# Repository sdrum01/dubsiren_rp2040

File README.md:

# DUB-IY Dub Siren with RP2040 CPU

DUBSIREN_rp2040 is a project designed to emulate a analog frequency generator for dub and reggae music. The result is the "**DUB-IY**" dub siren. 

Dub sirens are simple synthesizers without VCA (Voltage Controlled Amplifier) or VCF (Voltage Controlled Filter), but usually with a VCO (Voltage Controlled Oscillator) modulated by an LFO (Low Frequency Generator).

Such sirens are typically built with analog circuits. The challenge, however, was to optimize the parameter storage of digital solutions, simplify the electronics and to make it hackable.

**DUB-IY** is based on a Raspberry Pi Pico with an RP2040 CPU. It is fast enough to emulate VCOs and LFOs and offers sufficient options for internal data storage.

The Dub siren creates an square wave signal with an adjustable duty cycle. The sound can be modulated by two LFOs and an envelope generator to modulate the timing parameter. 

Finally, the signal is perfected with an integrated echo effect. 

The following values can be adjusted using potentiometers and switches:

* LFO1 waveform
(square, triple square, triangle, sawtooth, pulse)
* LFO2 waveform (square, triangle, sawtooth)
* Oscillator base frequency
* LFO1 and LFO2 frequency
* LFO1 and LFO2 contribution (negative and positive)
* Timing envelope contribution
* Oscillator waveform duty cycle
* LFO start retriggering
* Delay time (echo)
* Feedback (echo)
* Overall volume

The combination of LFOs 1 and 2 already produces many experimental siren sounds,
but the timing envelope adds significantly more dynamics to the sound.

>[!NOTE]
   >
   >This is a non-profit project with no goal of making big money.
   >It's purely for fun, and we assume no liability!
   
## Waiting List

To reserve one device or PCB pls write me an email: dub-iy@sdrum.elementfx.com

## Documentation

Have a look into the short introduction on YouTube:

- [DUB-IY Introduction](https://youtu.be/Yc06HZqR8gg?si=ktLNwQYJj4XRiWYL) 

There is also a manual explaining the various functions:

- [English Manual](docs/en/index.md)
- [Kurzanleitung Deutsch](docs/de/index.md)

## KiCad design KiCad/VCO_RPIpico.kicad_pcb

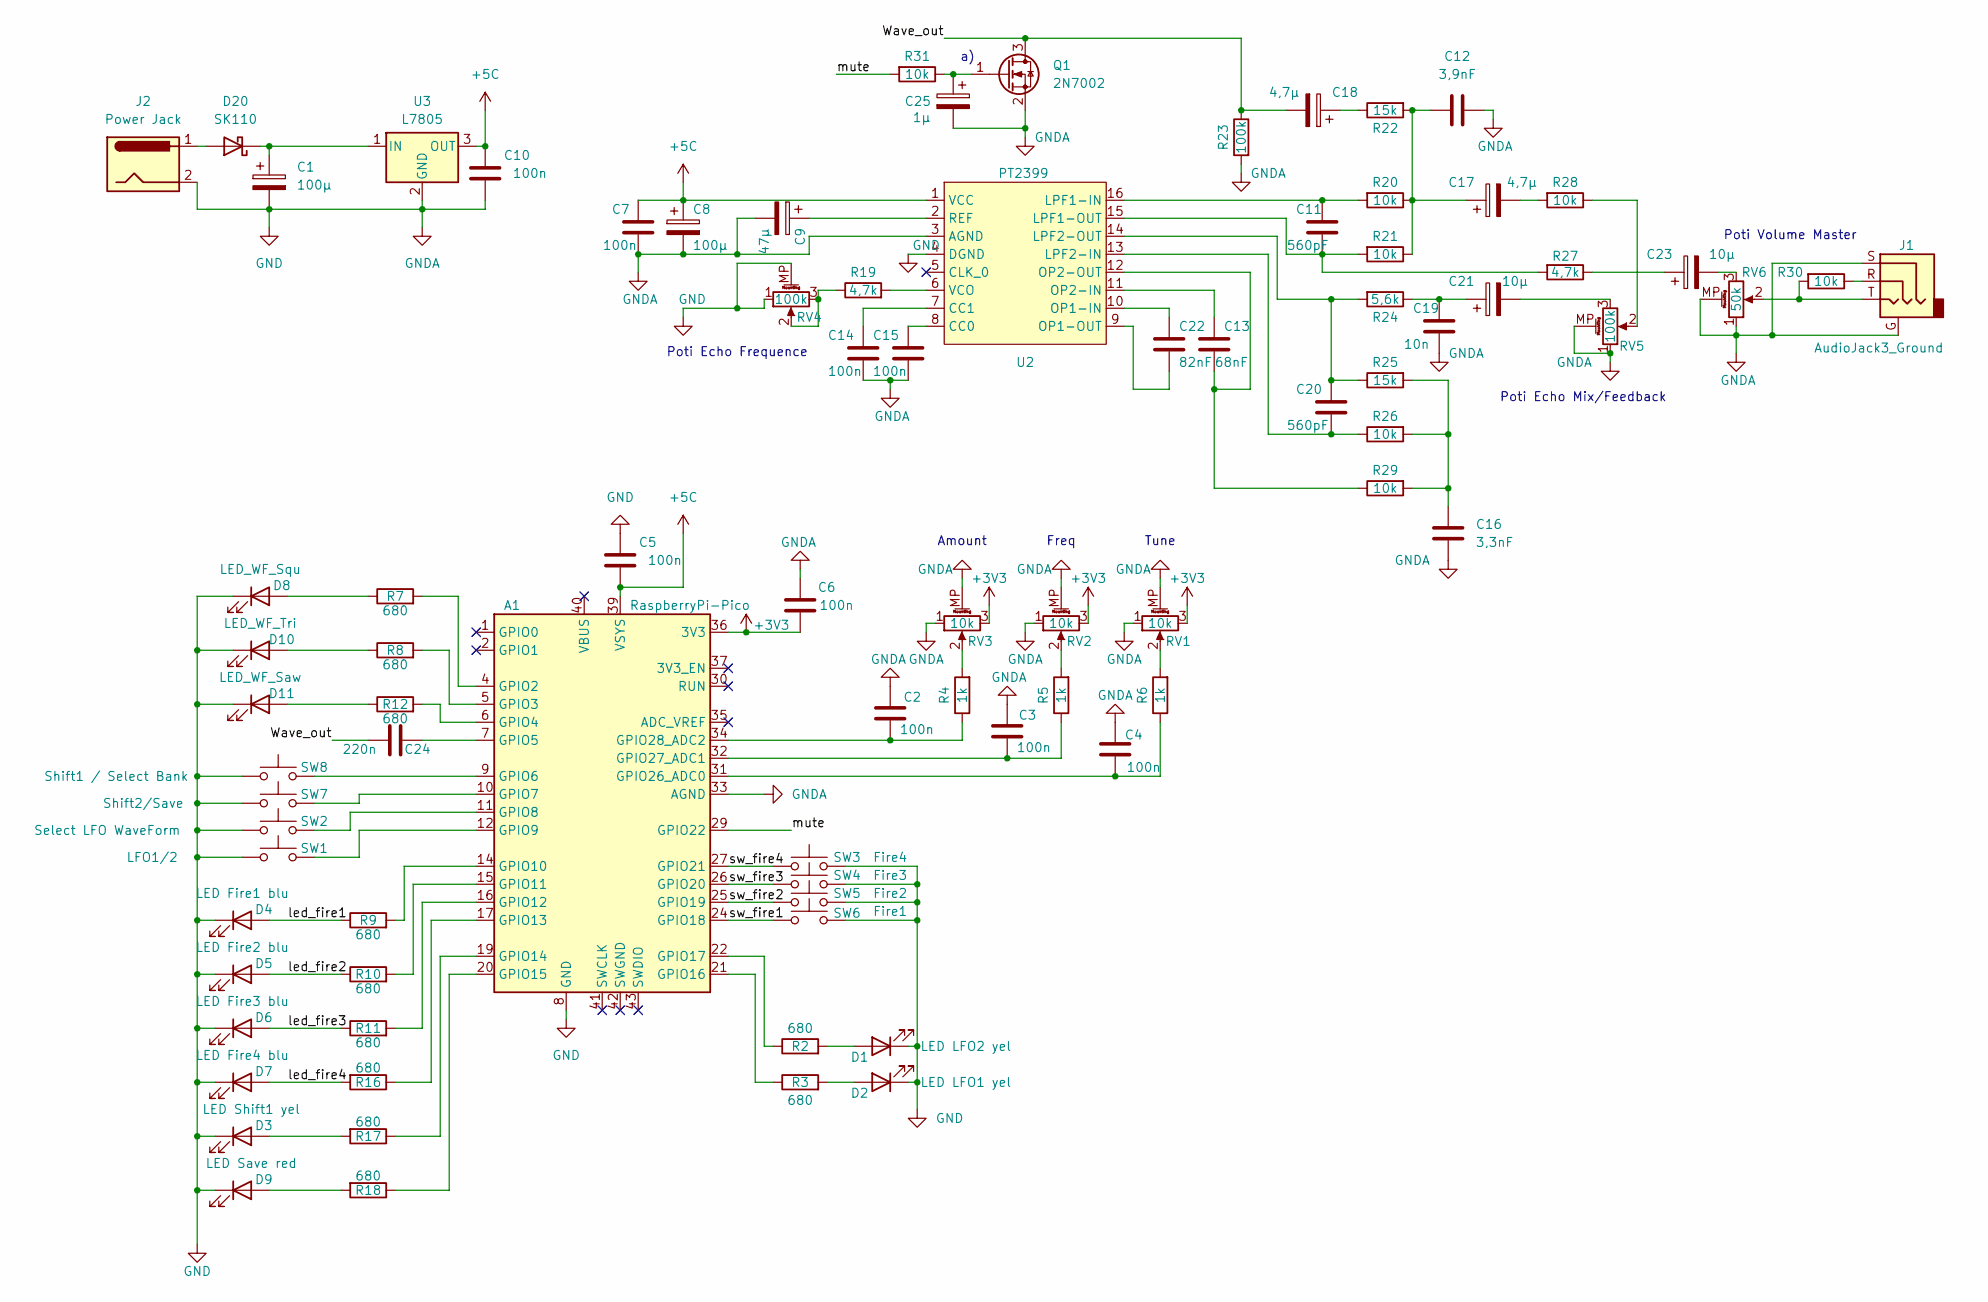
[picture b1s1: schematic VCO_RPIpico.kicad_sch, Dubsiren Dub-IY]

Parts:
A1: RaspberryPi-Pico; RPi_Pico_SMD_TH
C1, C8: 100µ; CP_Elec_6.3x5.8
C2, C3, C4, C5, C6, C7: 100n; C_1206_3216Metric
C9: 47µ; CP_Elec_6.3x5.3
C10, C14, C15: 100n; C_0805_2012Metric_Pad1.18x1.45mm_HandSolder
C11, C20: 560pF; C_0805_2012Metric_Pad1.18x1.45mm_HandSolder
C12: 3,9nF; C_0805_2012Metric_Pad1.18x1.45mm_HandSolder
C13: 68nF; C_0805_2012Metric_Pad1.18x1.45mm_HandSolder
C16: 3,3nF; C_0805_2012Metric_Pad1.18x1.45mm_HandSolder
C17, C18: 4,7µ; CP_EIA-2012-12_Kemet-R_Pad1.30x1.05mm_HandSolder
C19: 10n; C_0805_2012Metric_Pad1.18x1.45mm_HandSolder
C21, C23: 10µ; CP_Elec_4x5.7
C22: 82nF; C_0805_2012Metric_Pad1.18x1.45mm_HandSolder
C24: 220n; C_1206_3216Metric
C25: 1µ; CP_EIA-2012-12_Kemet-R_Pad1.30x1.05mm_HandSolder
D1: LED LFO2 yel; LED_D3.0mm
D2: LED LFO1 yel; LED_D3.0mm
D3: LED Shift1 yel; LED_D3.0mm
D4: LED Fire1 blu; LED_D3.0mm
D5: LED Fire2 blu; LED_D3.0mm
D6: LED Fire3 blu; LED_D3.0mm
D7: LED Fire4 blu; LED_D3.0mm
D8: LED_WF_Squ; LED_D3.0mm
D9: LED Save red; LED_D3.0mm
D10: LED_WF_Tri; LED_D3.0mm
D11: LED_WF_Saw; LED_D3.0mm
D20: SK110; D_SMA-SMB_Universal_Handsoldering
J1: AudioJack3_Ground; Jack_6.35mm_Neutrik_NMJ6HFD2_Horizontal
J2: Power Jack; BarrelJack_GCT_DCJ200-10-A_Horizontal
Q1: 2N7002; SOT-23
R2, R3, R7, R8, R9, R10, R11, R12, R16, R17, R18: 680; R_1206_3216Metric
R4, R5, R6: 1k; R_1206_3216Metric
R19, R27: 4,7k; R_1206_3216Metric
R20, R21, R26, R28, R29, R30, R31: 10k; R_1206_3216Metric
R22, R25: 15k; R_1206_3216Metric
R23: 100k; R_1206_3216Metric
R24: 5,6k; R_1206_3216Metric
RV1, RV2, RV3: 10k; Potentiometer_Alps_RK09K_Single_Vertical
RV4, RV5: 100k; Potentiometer_Alps_RK09K_Single_Vertical
RV6: 50k; Potentiometer_Alps_RK09K_Single_Vertical
SW1: LFO1/2; SW_PUSH_6mm
SW2: Select LFO WaveForm; SW_PUSH_6mm
SW3: Fire4; SW_PUSH_6mm
SW4: Fire3; SW_PUSH_6mm
SW5: Fire2; SW_PUSH_6mm
SW6: Fire1; SW_PUSH_6mm
SW7: Shift2/Save; SW_PUSH_6mm
SW8: Shift1 / Select Bank; SW_PUSH_6mm
U2: PT2399; DIP-16_W7.62mm_Socket_LongPads
U3: L7805; TO-252-3_TabPin2

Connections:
+3V3: A1.36 (3V3), C6.2, RV1.3, RV2.3, RV3.3
+5C: A1.39 (VSYS), C5.2, C7.1, C8.1, C10.1, U2.1 (VCC), U3.3 (OUT)
/Wave_out: C18.2, C24.1, Q1.3 (D), R23.1
/led_fire1: D4.2 (A), R9.1
/led_fire2: D5.2 (A), R10.1
/led_fire3: D6.2 (A), R11.1
/led_fire4: D7.2 (A), R16.2
/sw_fire1: A1.24 (GPIO18), SW6.1
/sw_fire2: A1.25 (GPIO19), SW5.1
/sw_fire3: A1.26 (GPIO20), SW4.1
/sw_fire4: A1.27 (GPIO21), SW3.1
GND: A1.3 (GND), A1.8 (GND), A1.13 (GND), A1.18 (GND), A1.23 (GND), A1.28 (GND), A1.33 (AGND), A1.38 (GND), C1.2, C2.1, C3.1, C4.1, C5.1, C6.1, C7.2, C8.2, C9.2, C10.2, C12.1, C14.2, C15.2, C16.2, C19.2, C25.2, D1.1 (K), D2.1 (K), D3.1 (K), D4.1 (K), D5.1 (K), D6.1 (K), D7.1 (K), D8.1 (K), D9.1 (K), D10.1 (K), D11.1 (K), J1.G, J1.S, J2.2, Q1.2 (S), R23.2, RV1.1, RV1.MP (MountPin), RV2.1, RV2.MP (MountPin), RV3.1, RV3.MP (MountPin), RV4.1, RV4.MP (MountPin), RV5.1, RV5.MP (MountPin), RV6.1, RV6.MP (MountPin), SW1.1, SW2.1, SW3.2, SW4.2, SW5.2, SW6.2, SW7.1, SW8.1, U2.3 (AGND), U2.4 (DGND), U3.2 (GND)
unnamed: A1.4 (GPIO2), R7.2
unnamed: A1.5 (GPIO3), R8.2
unnamed: A1.6 (GPIO4), R12.2
unnamed: A1.7 (GPIO5), C24.2
unnamed: A1.9 (GPIO6), SW8.2
unnamed: A1.10 (GPIO7), SW7.2
unnamed: A1.11 (GPIO8), SW2.2
unnamed: A1.12 (GPIO9), SW1.2
unnamed: A1.14 (GPIO10), R9.2
unnamed: A1.15 (GPIO11), R10.2
unnamed: A1.16 (GPIO12), R11.2
unnamed: A1.17 (GPIO13), R16.1
unnamed: A1.19 (GPIO14), R17.1
unnamed: A1.20 (GPIO15), R18.1
unnamed: A1.21 (GPIO16), R3.1
unnamed: A1.22 (GPIO17), R2.1
unnamed: A1.31 (GPIO26_ADC0), C4.2, R6.1
unnamed: A1.32 (GPIO27_ADC1), C3.2, R5.1
unnamed: A1.34 (GPIO28_ADC2), C2.2, R4.1
unnamed: C12.2, C17.1, R20.1, R21.1, R22.2
unnamed: C16.1, R25.2, R26.2, R29.2
unnamed: C17.2, R28.2
unnamed: C18.1, R22.1
unnamed: C19.1, C21.1, R24.1
unnamed: C21.2, RV5.3
unnamed: C23.1, R27.1
unnamed: C23.2, RV6.3
unnamed: C25.1, Q1.1 (G), R31.1
unnamed: D1.2 (A), R2.2
unnamed: D2.2 (A), R3.2
unnamed: D3.2 (A), R17.2
unnamed: D8.2 (A), R7.1
unnamed: D9.2 (A), R18.2
unnamed: D10.2 (A), R8.1
unnamed: D11.2 (A), R12.1
unnamed: D20.2 (A), J2.1
unnamed: C1.1, D20.1 (K), U3.1 (IN)
unnamed: J1.R, R30.1
unnamed: J1.T, R30.2, RV6.2
unnamed: R4.2, RV3.2
unnamed: R5.2, RV2.2
unnamed: R6.2, RV1.2
unnamed: R19.1, RV4.2, RV4.3
unnamed: R28.1, RV5.2
unnamed: A1.29 (GPIO22), R31.2
unnamed: C15.1, U2.8 (CC0)
unnamed: C14.1, U2.7 (CC1)
unnamed: C11.1, R20.2, U2.16 (LPF1-IN)
unnamed: C11.2, R21.2, R27.2, U2.15 (LPF1-OUT)
unnamed: C20.2, R26.1, U2.13 (LPF2-IN)
unnamed: C20.1, R24.2, R25.1, U2.14 (LPF2-OUT)
unnamed: C22.1, U2.10 (OP1-IN)
unnamed: C22.2, U2.9 (OP1-OUT)
unnamed: C13.1, U2.11 (OP2-IN)
unnamed: C13.2, R29.1, U2.12 (OP2-OUT)
unnamed: C9.1, U2.2 (REF)
unnamed: R19.2, U2.6 (VCO)

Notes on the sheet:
Poti Echo Mix/Feedback
Freq
Poti Echo Frequence
Tune
Poti Volume Master
Amount

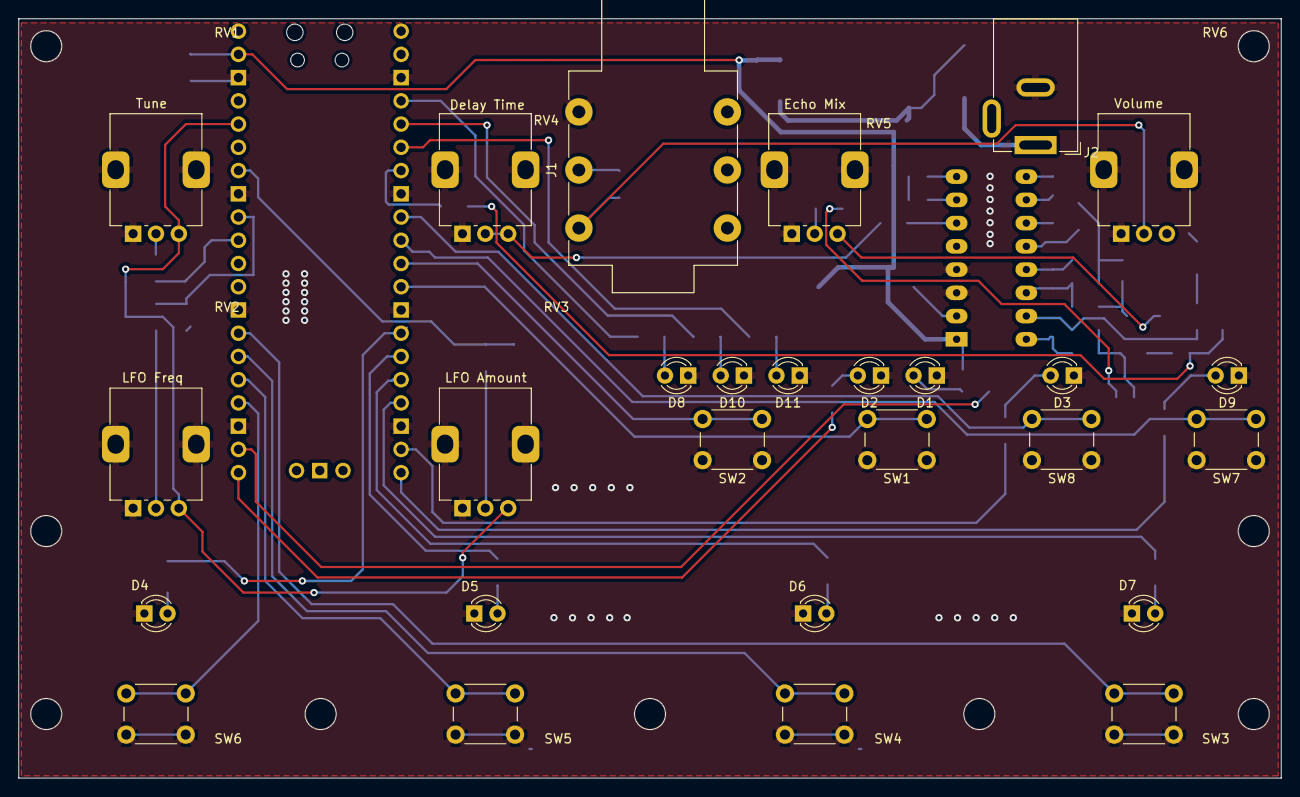
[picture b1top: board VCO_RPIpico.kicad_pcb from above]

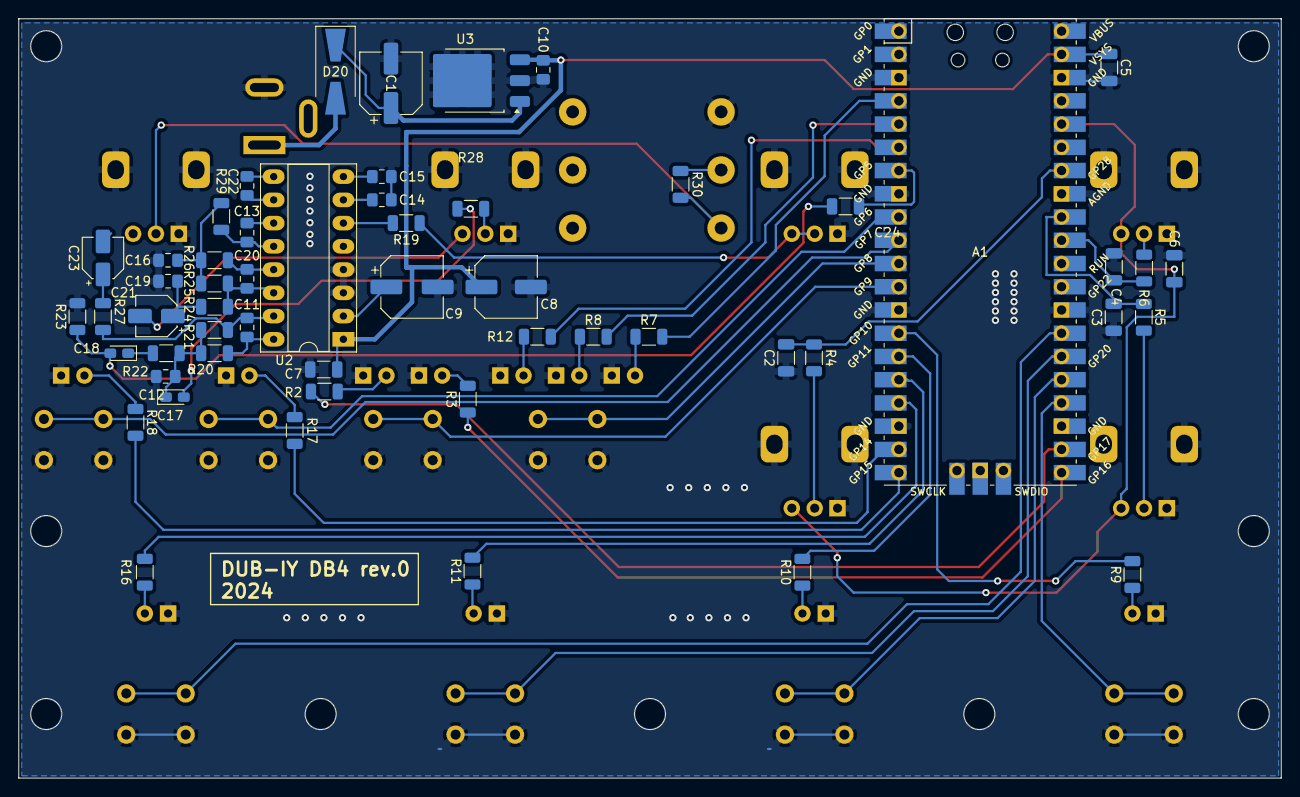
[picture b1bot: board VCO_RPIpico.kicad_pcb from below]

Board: 2 copper layers, 138.0 x 83.0 mm, 81 parts (54 on the bottom side), 67 nets.

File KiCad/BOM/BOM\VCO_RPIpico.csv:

"Reference","Value","Datasheet","Footprint","Qty","DNP","Reichelt"
"A1","RaspberryPi-Pico","https://datasheets.raspberrypi.com/pico/pico-datasheet.pdf","MCU_RaspberryPi_and_Boards:RPi_Pico_SMD_TH","1","","RASP PI PICO H "
"C1,C8","100µ","~","Capacitor_SMD:CP_Elec_6.3x5.8","2","","FT-V 100U 16 "
"C2,C3,C4,C5,C6,C7,C10,C14,C15","100n","~","-- verschiedene Werte --","9","",""
"C9","47µ","~","Capacitor_SMD:CP_Elec_6.3x5.3","1","","ELN RVS-16V470MU "
"C11,C20","560pF","~","Capacitor_SMD:C_0805_2012Metric_Pad1.18x1.45mm_HandSolder","2","",""
"C12","3,9nF","~","Capacitor_SMD:C_0805_2012Metric_Pad1.18x1.45mm_HandSolder","1","",""
"C13","68nF","~","Capacitor_SMD:C_0805_2012Metric_Pad1.18x1.45mm_HandSolder","1","",""
"C16","3,3nF","~","Capacitor_SMD:C_0805_2012Metric_Pad1.18x1.45mm_HandSolder","1","",""
"C17,C18","4,7µ","~","Capacitor_Tantalum_SMD:CP_EIA-2012-12_Kemet-R_Pad1.30x1.05mm_HandSolder","2","","KEM X5R0805 4,7U "
"C19","10n","~","Capacitor_SMD:C_0805_2012Metric_Pad1.18x1.45mm_HandSolder","1","",""
"C21,C23","10µ","~","Capacitor_SMD:CP_Elec_4x5.7","2","","SMD ELKO 10/16 "
"C22","82nF","~","Capacitor_SMD:C_0805_2012Metric_Pad1.18x1.45mm_HandSolder","1","",""
"C24","220n","~","Capacitor_SMD:C_1206_3216Metric","1","",""
"D1","LED LFO2","~","LED_THT:LED_D3.0mm","1","",""
"D2","LED LFO1","~","LED_THT:LED_D3.0mm","1","",""
"D3","LED Shift1","~","LED_THT:LED_D3.0mm","1","",""
"D4","LED Fire1","~","LED_THT:LED_D3.0mm","1","",""
"D5","LED Fire2","~","LED_THT:LED_D3.0mm","1","",""
"D6","LED Fire3","~","LED_THT:LED_D3.0mm","1","",""
"D7","LED Fire4","~","LED_THT:LED_D3.0mm","1","",""
"D8","LED_WF_Squ","~","LED_THT:LED_D3.0mm","1","",""
"D9","LED Shift2","~","LED_THT:LED_D3.0mm","1","",""
"D10","LED_WF_Tri","~","LED_THT:LED_D3.0mm","1","",""
"D11","LED_WF_Saw","~","LED_THT:LED_D3.0mm","1","",""
"D20","SK110","~","Diode_SMD:D_SMA-SMB_Universal_Handsoldering","1","",""
"J1","AudioJack3_Ground","~","Audiosockets:Jack_3.5mm_Ledino_KB3SPRS_Horizontal","1","","EBS 35 "
"J2","Power Jack","~","Connector_BarrelJack:BarrelJack_GCT_DCJ200-10-A_Horizontal","1","","CLIFF FCR681465 "
"R2,R3,R7,R8,R9,R10,R11,R12,R16,R17,R18","680","~","Resistor_SMD:R_1206_3216Metric","11","",""
"R4,R5,R6","1k","~","Resistor_SMD:R_1206_3216Metric","3","",""
"R19,R27","4,7k","~","Resistor_SMD:R_1206_3216Metric","2","",""
"R20,R21,R26,R28,R29,R30,RV1,RV2,RV3","10k","~","-- verschiedene Werte --","9","","RK09K113-LIN10K "
"R22,R25","15k","~","Resistor_SMD:R_1206_3216Metric","2","",""
"R23,RV4,RV5","100k","~","-- verschiedene Werte --","3","","RK09K113-LIN100K "
"R24","5,6k","~","Resistor_SMD:R_1206_3216Metric","1","",""
"RV6","50k","~","poti_alps:Potentiometer_Alps_RK09K_Single_Vertical","1","","RK09K113-LIN50K "
"SW1","LFO1/2","~","Button_Switch_THT:SW_PUSH_6mm","1","","OMR B3F-1002"
"SW2","Select LFO WaveForm","~","Button_Switch_THT:SW_PUSH_6mm","1","","OMR B3F-1002"
"SW3","Fire4","~","Button_Switch_THT:SW_PUSH_6mm","1","","RAFI 100.502 "
"SW4","Fire3","~","Button_Switch_THT:SW_PUSH_6mm","1","","RAFI 100.502 "
"SW5","Fire2","~","Button_Switch_THT:SW_PUSH_6mm","1","","RAFI 100.502 "
"SW6","Fire1","~","Button_Switch_THT:SW_PUSH_6mm","1","","RAFI 100.502 "
"SW7","Shift2/Save","~","Button_Switch_THT:SW_PUSH_6mm","1","","OMR B3F-1002"
"SW8","Shift1 / Select Bank","~","Button_Switch_THT:SW_PUSH_6mm","1","","OMR B3F-1002"
"U2","PT2399","","Package_DIP:DIP-16_W7.62mm_Socket_LongPads","1","",""
"U3","L7805","http://www.st.com/content/ccc/resource/technical/document/da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","Package_TO_SOT_SMD:TO-252-3_TabPin2","1","","L78M05CDT STM "

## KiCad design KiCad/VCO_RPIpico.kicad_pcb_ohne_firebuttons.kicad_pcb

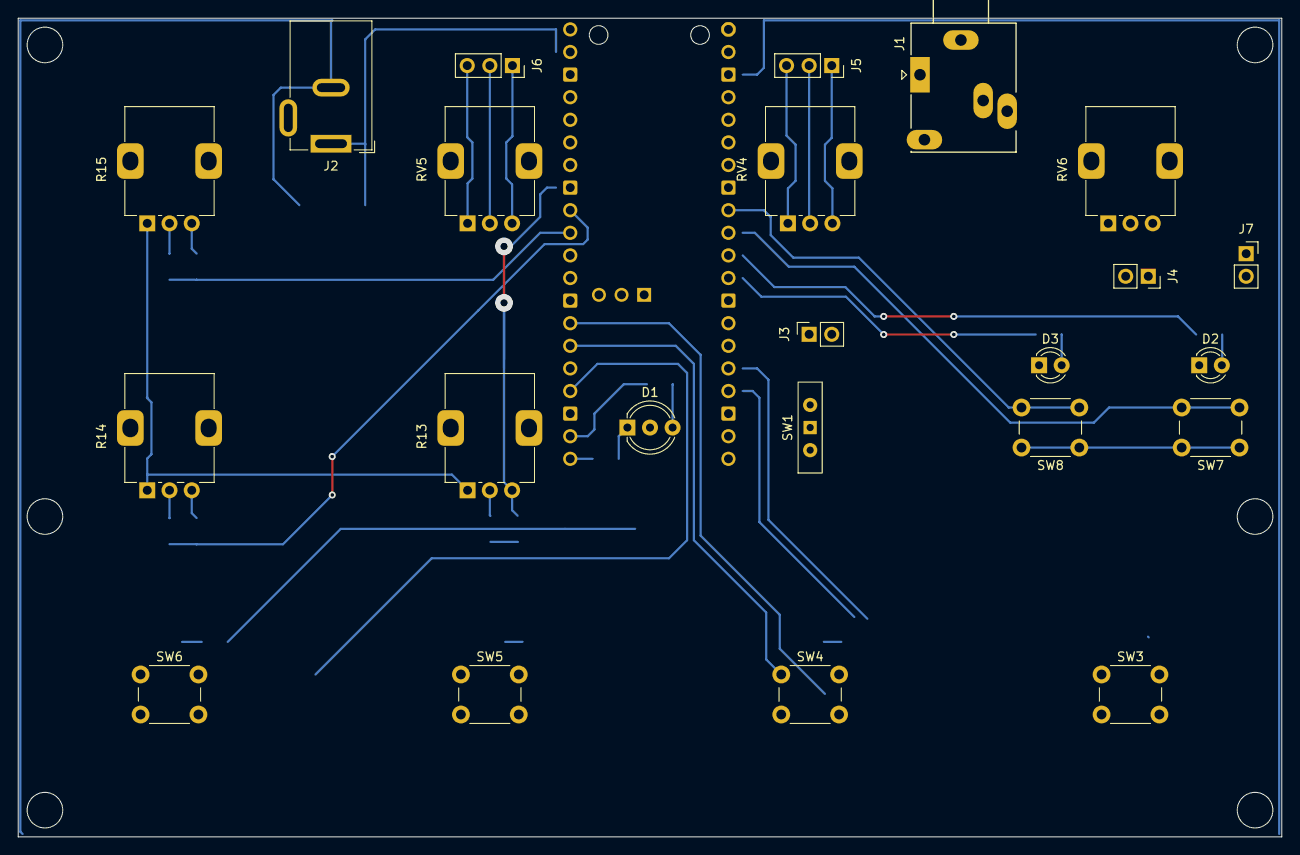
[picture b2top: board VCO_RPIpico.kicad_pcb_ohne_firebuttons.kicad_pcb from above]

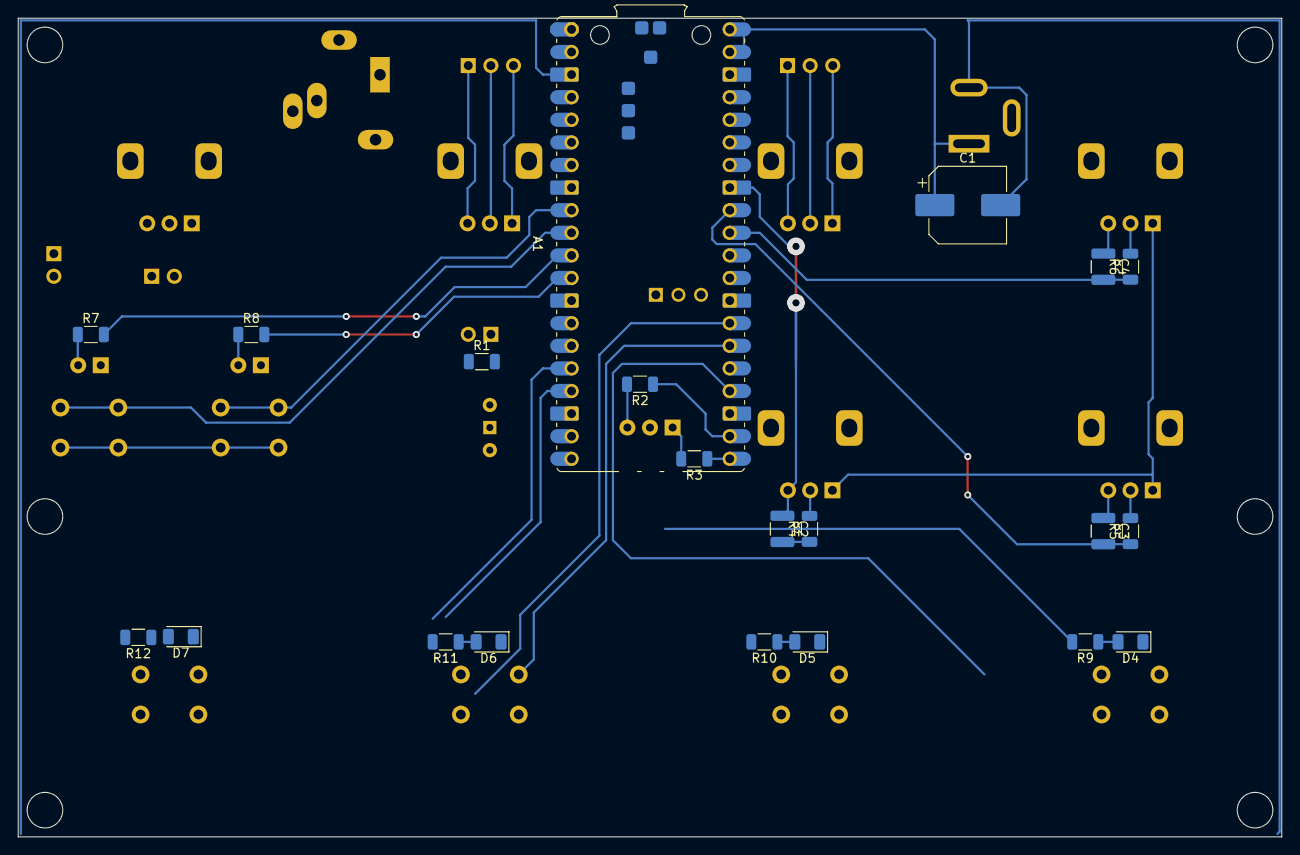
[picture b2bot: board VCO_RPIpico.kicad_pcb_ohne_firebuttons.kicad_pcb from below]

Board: 2 copper layers, 142.0 x 92.0 mm, 44 parts (21 on the bottom side), 44 nets.

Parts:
A1: RaspberryPi-Pico; Raspberry_Pi_Pico_SMT_THT_noDebugPort
C1: 100µ; CP_Elec_8x10.5
C2, C3, C4: 100n; C_1210_3225Metric
D1: LED_Dual_AKA; LED_D5.0mm-3
D2: LED Shift1; LED_D3.0mm
D3: LED Shift2; LED_D3.0mm
D4: LED Fire1; LED_1206_3216Metric
D5: LED Fire2; LED_1206_3216Metric
D6: LED Fire3; LED_1206_3216Metric
D7: LED Fire4; LED_1206_3216Metric
J1: AudioJack2; Jack_3.5mm_Ledino_KB3SPRS_Horizontal
J2: Power Jack 5V; BarrelJack_GCT_DCJ200-10-A_Horizontal
J3: Wave Out; PinSocket_1x02_P2.54mm_Vertical
J4: Echo Out; PinSocket_1x02_P2.54mm_Vertical
J5: Poti Echo Mix/Feedback; PinSocket_1x03_P2.54mm_Vertical
J6: Poti Echo Freq; PinSocket_1x03_P2.54mm_Vertical
J7: Echo Power; PinSocket_1x02_P2.54mm_Vertical
R1, R4, R5, R6: 1k; R_1206_3216Metric
R2, R3, R7, R8, R9, R10, R11, R12: 100; R_1206_3216Metric
R13, R14, R15: 100k; Potentiometer_Alps_RK09K_Single_Vertical
RV4, RV5: 100k; Potentiometer_Alps_RK09K_Single_Vertical
RV6: 50k; Potentiometer_Alps_RK09K_Single_Vertical
SW1: LFO Waveform; SW_Slide-03_Wuerth-WS-SLTV_10x2.5x6.4_P2.54mm
SW3: Fire4; SW_PUSH_6mm
SW4: Fire3; SW_PUSH_6mm
SW5: Fire2; SW_PUSH_6mm
SW6: Fire1; SW_PUSH_6mm
SW7: Shift2/Save; SW_PUSH_6mm
SW8: Shift1; SW_PUSH_6mm

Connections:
+3V3: A1.36 (3V3), R13.1, R14.1, R15.1
+5C: A1.39 (VSYS), A1.40 (VBUS), C1.1, J2.1, J7.2
GND: A1.3 (GND), A1.8 (GND), A1.13 (GND), A1.18 (GND), A1.23 (GND), A1.28 (GND), A1.38 (GND), C1.2, D1.2 (K), D2.1 (K), D3.1 (K), D4.1 (K), D5.1 (K), D6.1 (K), D7.1 (K), J1.T, J2.2, J3.1, J4.2, J7.1, RV6.1, SW1.2 (B), SW3.2, SW4.2, SW5.2, SW6.2, SW7.1, SW8.1
GNDA: A1.33 (AGND), C2.1, C3.1, C4.1, R13.3, R14.3, R15.3
unnamed: A1.5 (GPIO3), SW1.1 (A)
unnamed: A1.6 (GPIO4), SW1.3 (C)
unnamed: A1.7 (GPIO5), R1.2
unnamed: A1.9 (GPIO6), SW8.2
unnamed: A1.10 (GPIO7), SW7.2
unnamed: A1.11 (GPIO8), R7.2
unnamed: A1.12 (GPIO9), R8.2
unnamed: A1.14 (GPIO10), R9.2
unnamed: A1.15 (GPIO11), R10.2
unnamed: A1.16 (GPIO12), R11.2
unnamed: A1.17 (GPIO13), R12.2
unnamed: A1.21 (GPIO16), R3.1
unnamed: A1.22 (GPIO17), R2.1
unnamed: A1.24 (GPIO18), SW6.1
unnamed: A1.25 (GPIO19), SW5.1
unnamed: A1.26 (GPIO20), SW4.1
unnamed: A1.27 (GPIO21), SW3.1
unnamed: A1.31 (GPIO26_ADC0), C4.2, R6.1
unnamed: A1.32 (GPIO27_ADC1), C3.2, R5.1
unnamed: A1.34 (GPIO28_ADC2), C2.2, R4.1
unnamed: D1.1 (A1), R3.2
unnamed: D1.3 (A2), R2.2
unnamed: D2.2 (A), R7.1
unnamed: D3.2 (A), R8.1
unnamed: D4.2 (A), R9.1
unnamed: D5.2 (A), R10.1
unnamed: D6.2 (A), R11.1
unnamed: D7.2 (A), R12.1
unnamed: J1.S, RV6.2
unnamed: J3.2, R1.1
unnamed: J4.1, RV6.3
unnamed: J5.1, RV4.3
unnamed: J5.2, RV4.2
unnamed: J5.3, RV4.1
unnamed: J6.1, RV5.3
unnamed: J6.2, RV5.2
unnamed: J6.3, RV5.1
unnamed: R4.2, R13.2
unnamed: R5.2, R14.2
unnamed: R6.2, R15.2

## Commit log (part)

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2024-08-07 Potis abgefragt
2024-08-10 transfer LFO mit 3 Waveforms
2024-08-13 LFO Anpassungen
2024-08-15 Antilog-Konverter
2024-08-18 WaveFormFunktionsschalter für LFO und verschieben des LFO Arbeitspunkt
2024-08-27 PWM LED als Anzeige
2024-08-29 LEDs eingebunden
2024-09-02 Envelope added
2024-09-03 Envelope auf Multiplikator 1 auslaufen lassen
2024-09-04 test
2024-09-04 test dev
2024-09-04 KiCad DAten erfasst
2024-09-04 KiCad cleaned
2024-09-04 test commit
2024-09-08 Amount in die Mitte gerückt, um pos und neg Beeinflussung ohne extra Funktion zu haben
2024-09-12 Teiler für PWM bei LEDs
2024-09-15 Potiänderung auswerten
2024-09-15 littleFS test
2024-09-16 Bounce2 implementiert
2024-09-18 auf Bounce2 für Buttons umgestellt und Implementierung JSON
2024-09-19 Kicas
2024-09-19 .gitignore
2024-09-22 Speichern dere Werte per JSOM
2024-09-22 State changed on Waveformswitch
2024-09-22 Save Values and Load Values
2024-09-22 Shiftstate statt WaveformFunctions-schalter für Umschaltung der LFO/Envelop
2024-09-22 test duty
2024-09-23 gitignore angepasst
2024-09-23 Korrektur und KiCad
2024-09-26 DutyCycle added
2024-09-27 Schaltung erweitert um 2 Shhifttasten
2024-09-27 Schaltung geändert
2024-09-27 CAD-Daten aus Onshape
2024-09-28 2 Shifttasten eingebaut
2024-09-28 Shiftstate als Byte, Reset des env.durch Sh1+2
2024-09-29 logpress prepared
2024-09-29 Sound Hold with long press fire
2024-09-29 Auslenkung LFO erhöht
2024-09-30 Kicad Schematic and Board
2024-09-30 PCB and Schematic
2024-09-30 Projectfile Updated
2024-10-01 2 Shift LEDs
2024-10-02 Shift Knob Added
2024-10-02 Files added
2024-10-02 KiCad
2024-10-03 LongPress durch Drücken des Nachbarbutton und Save korrigiert
2024-10-05 LFO2 statt Envelopegenerator
2024-10-10 LFO 2 mit 3 WaveForms
2024-10-10 Envelope Test
2024-10-11 Envelope als Timing-Parameter für LFO1
2024-10-11 Envelope fertig implementiert mit Speichermöglichkeit, Bank 1..4 für Speicherplatz 1..16
2024-10-13 Testroutine Default Sound, nach Bankwechsel keine Tonerzeugung, Wechsel der Bank zum kopieren möglich
2024-10-13 Envelope auch auf LFO2
2024-10-13 debug timing wegen hänger LFO2
2024-10-13 Retriggern LFO unterdrücken bei Longpress
2024-10-14 Kicad weiter, Blink
2024-10-14 modifiziertes Boardlayout
2024-10-15 ignore mod
2024-10-15 COde workspace removed
2024-10-15 Implement Blink, Test Reset LFO2
2024-10-16 Waveform select switch
2024-10-19 KiCad weiter
2024-10-19 vom Kippschalter umgestellt auf Button zur FLO Waveform Auswahl
2024-10-20 4 LEDS für FIreButtons
2024-10-20 KiCad und Gitignore: Backups ignorieren
2024-10-22 Back to the Kippschalter als LFOWaveForm
2024-10-23 Datenblatt Schalter
2024-10-24 Korrektur StateChange und Anzeige dews letzten Firebuttons
2024-10-25 gitignore Backups CAD excluded
2024-10-27 Test Matrix
2024-10-28 KiCad MatrixLED und Bauteil für Echo
2024-10-28 remove backupd folder
2024-10-28 CAM Settings added
2024-10-28 Export STL Body
2024-10-28 noch ein Export aus CAD
2024-10-30 LED Matrix weiter
2024-11-03 Button für selectWaveForm statt Schalter
2024-11-03 LFOWaveForm Switch und Anzeige nach aktueller Waveform gesetzt
2024-11-09 Umgestellt auf einfache LED Pinansteuerung
2024-11-11 Kicad PCB
2024-11-11 datasheet PT2399 Echo IC
2024-11-12 Echomodul diskret mit PT2399 implementiert
2024-11-12 Sorcecode: Umgestellt auf einfache LED-Ansteuerung
2024-11-13 PCB Layout
2024-11-13 PCB neue Taster
2024-11-13 PCB fertig, Gerber Export
2024-11-13 zusätzliche LEDs unter die kleinen FIre-Button
2024-11-13 Ansicht angepasst
2024-11-14 Kicad Schottkydiode added
2024-11-14 Kicad kleine Änderung
2024-11-14 Kicad Bezeichner hinzugefügt
2024-11-14 KiCad Nullserie finished
2024-11-17 optionsFlags implementiert
2024-11-17 cleanup
2024-11-19 LED des letzt gespielten Tons blinkt im IDLE
2024-11-24 Bugfix: nach einschalten wurden bei FB1 die Parameter statt aus gespeicherten Daten von den Potis genommen
2024-11-24 Values im Board wieder eingeblendet
2024-11-25 PCB values enabled
2024-11-27 3D Print STL Files added
2024-11-30 clean Up, Adaptions to Board rev.0, Dump receive as JSON
2024-12-02 Gehäuseänderung
2024-12-02 STL FIles
2024-12-08 Frontplatte DXF
2024-12-09 STL Files added
2024-12-09 per Inkscape Frontplatte erstellt
2024-12-12 CAD: DXF Frontplatte, STL FIles
2024-12-12 CAD: DXF Frontplatte korrigiert
2024-12-13 CAD new STL Files
2024-12-14 CAD: Frontplatte CAD/CAM
2024-12-14 CAD: Potiknop angepasst, C: Letzter Firebutton bei Longpress korrigiert
2024-12-17 manual.md aktualisieren
2024-12-27 CAD: STL V12
2024-12-29 CAD: neuer Slim-Deckel
2024-12-30 DUku
2025-01-02 CAD: Body V12.2
2025-01-06 CAD: Shiftknopf 8mm
2025-01-06 File renamed
2025-01-07 CAD und eCAD
2025-01-23 CAD: Body V12.3
2025-01-25 CAM Frontplatte
2025-01-25 Flags werden nicht mehr überladen bei Fire, bei save leuchtet Fire dauernd
2025-01-25 Firmware added
2025-01-31 CAD neue STL Version Gehäuse
2025-02-23 Rasterung im Square unter Amp.0
2025-02-23 3-er Raster im negativen Bereich von Rechteck LFO
2025-02-23 Firmware Version 1.2
2025-02-23 Aktualisieren von README.md
2025-02-28 Test mit 3-Ton Rechteck
2025-03-03 CAD: STL Files added
2025-03-06 CAD Potiknob STL
2025-03-06 CAD STP deleted
2025-03-13 KiCad: Supplier added for some parts
2025-03-18 KiCad: Schaltplan angepasst
2025-03-22 gitignore
2025-03-22 KiCad BOM erstellt
2025-03-30 KiCad änderungen
2025-03-30 defekte datei gelöscht
2025-03-30 Frontplatte Logo DUB-IY
2025-03-31 test mit rasterisierung des tons
2025-04-10 CAM Files moved
2025-04-21 One Time Shot (LFO1) for Optionsflag2 ; Amp Factor 2 for Flag 3
2025-04-21 new Firmwarefiles
2025-05-04 new CAD/CAM Files
2025-05-12 logo added
2025-05-12 manual draft shift in doku
2025-05-12 unused file deleted
2025-05-19 stage
2025-06-04 drawings added
2025-06-06 python script for datatransfer dump data
2025-06-07 data transfer tool for send and receive dumps
2025-06-08 weiter an receiveDump
2025-06-09 dataTransfer first version finneshed and ino file extended to dataTransfer
2025-06-09 help text in dataTransfer.py
2025-06-11 businesscard draft
2025-06-11 businesscard V2
2025-06-12 sound examples
2025-06-15 manual.md erstellen
2025-06-18 BOM reworked
2025-06-18 BOM extended
2025-06-18 new graphic of front for card
2025-06-18 dump examples
2025-06-18 doku features overview
2025-06-18 2.manual.md gelöscht
2025-06-19 BOM moved
2025-06-19 BOM ods
2025-06-20 Remove .DS_Store from version control
2025-06-20 neues Dump aus seriennummer 0007
2025-06-20 manual weitergeschrieben
2025-06-20 Aktualisieren von manual.md
2025-06-25 manual pdf
2025-06-25 Grafik für Manual
2025-06-25 Update manual.md test
2025-06-25 SVG1
2025-06-25 SVG überarbeitet
2025-06-27 Doku PNG Waveformmodulation
2025-06-27 nochmal PNGs für Wellenformdoku
2025-06-27 manual updated, diagrams inserted
2025-06-27 folder doku renamed into docs
2025-06-28 fix manual
2025-06-28 use alert boxes
2025-06-29 temp short manual deleted
2025-07-05 nwe grafik
2025-07-05 new grafik
2025-07-05 grafik mit einfacher sägezahnwellenform hinzu
2025-07-08 index.md aktualisieren
2025-07-09 new pictures, update
2025-07-09 next Grafik
2025-07-09 manual ger: knob rewoorked
2025-07-13 new svg
2025-07-13 svg4
2025-07-13 svg rect_int
2025-07-13 update manual ger
2025-07-13 english manual
2025-07-13 update eng man
2025-07-14 rename language folders
2025-07-14 update english version
2025-07-14 fix some typos
2025-07-14 update english translation
2025-07-14 fix link
2025-07-14 updates README
2025-07-14 add documentation section
2025-07-14 change wording
2025-07-15 Edit and translation short manual
    * rename language folders
    * update english version
    * fix some typos
    * update english translation
    * fix link
    * updates README
2025-07-15 new index.md in docs root
2025-07-15 index.md in docs folder
2025-07-18 head picture in main md file for short manual
2025-07-18 graphic frame border fix
2025-07-20 avoid noisy click with changing the mode of SoundPin to input when no tone is play
2025-11-28 PCB correctur
2026-03-30 korrektur 260330
2026-04-09 PCB rework
